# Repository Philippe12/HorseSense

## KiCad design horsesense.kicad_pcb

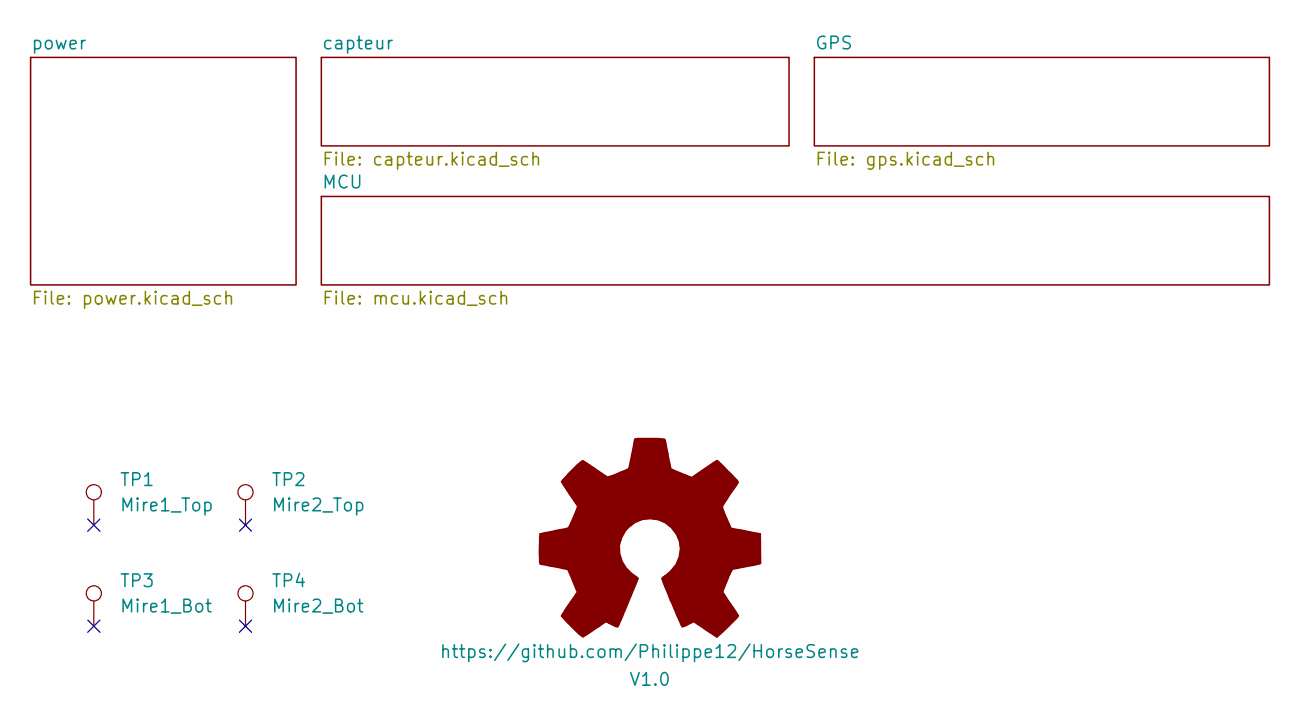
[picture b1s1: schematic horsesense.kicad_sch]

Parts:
SYM1: https://github.com/Philippe12/HorseSense; OSHW-Symbol_13.4x12mm_SilkScreen
TP1: Mire1_Top; TestPoint_Pad_D1.0mm
TP2: Mire2_Top; TestPoint_Pad_D1.0mm
TP3: Mire1_Bot; TestPoint_Pad_D1.0mm
TP4: Mire2_Bot; TestPoint_Pad_D1.0mm

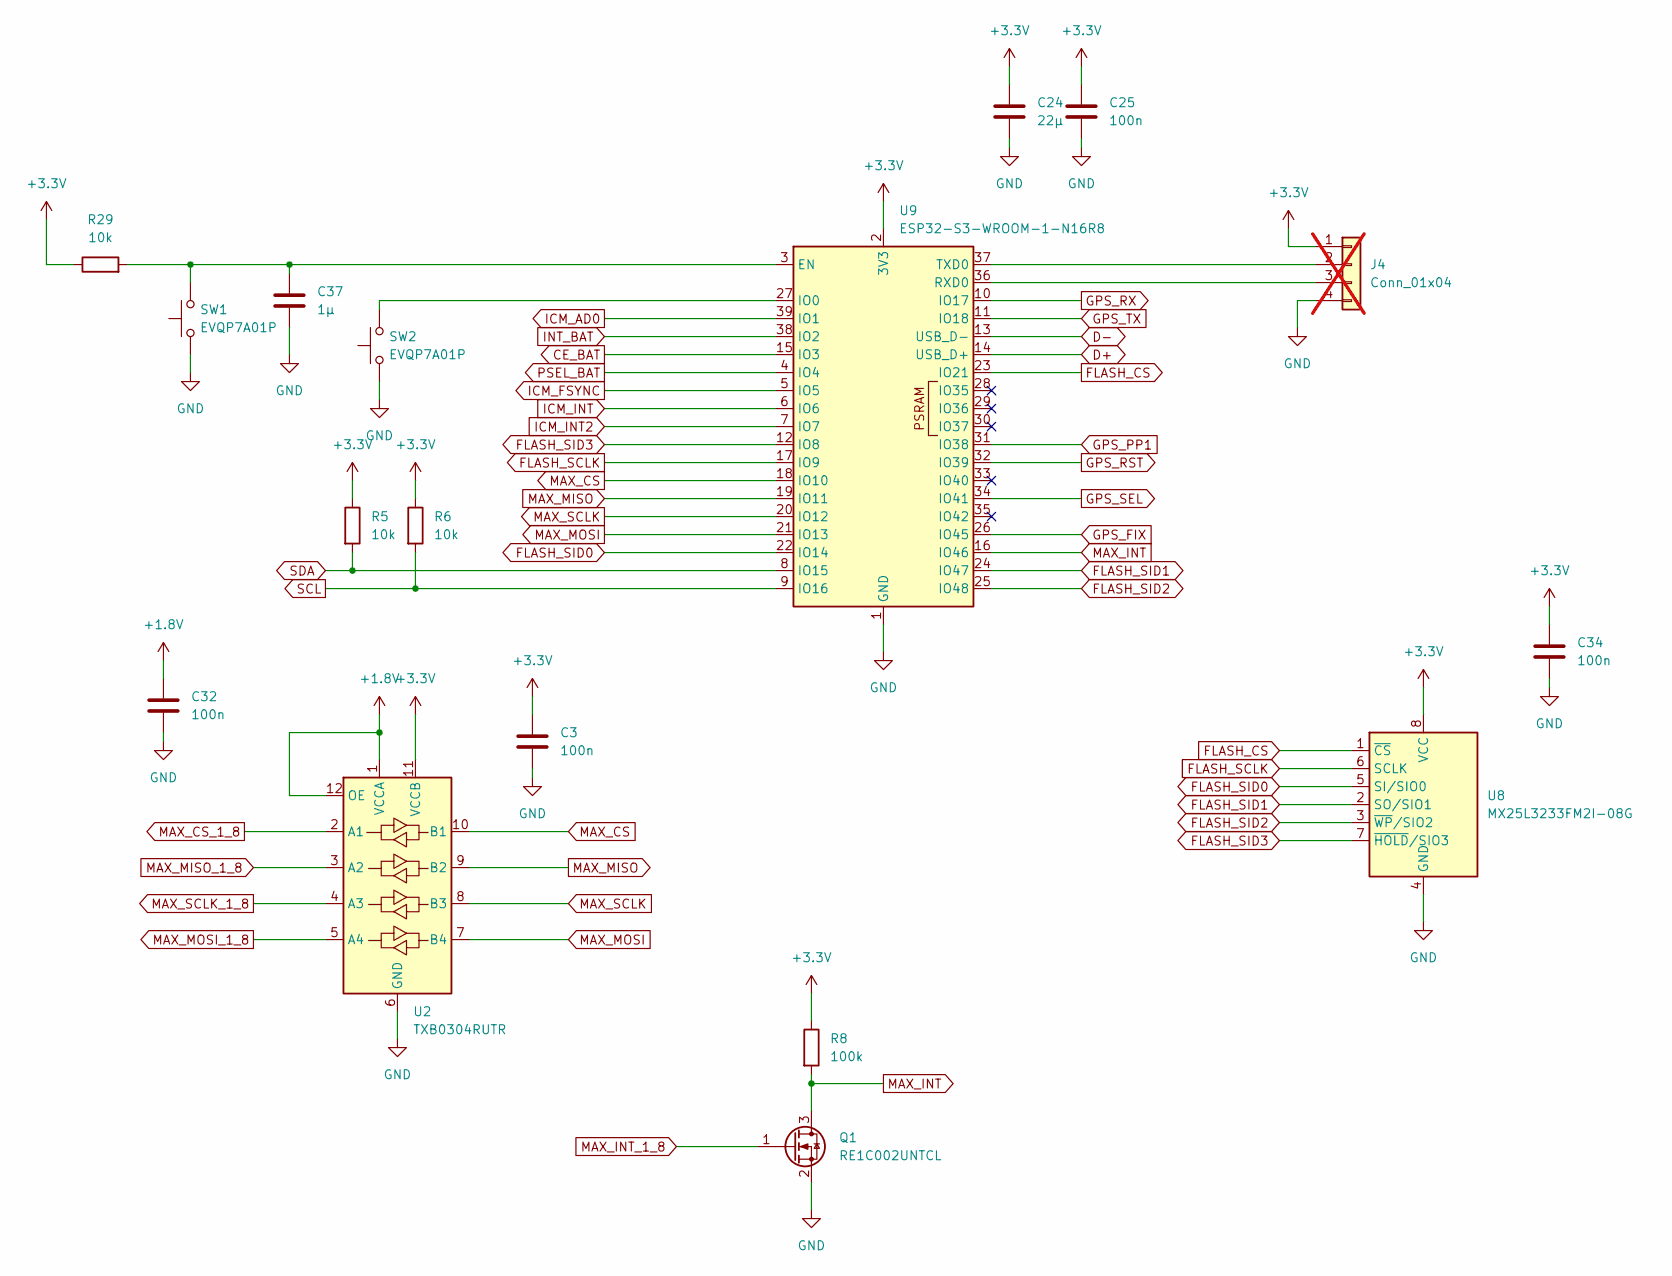
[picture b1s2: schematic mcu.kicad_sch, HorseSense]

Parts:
C3, C25, C32, C34: 100n; C_0805_2012Metric; JLCPCB Part # C1711
C24: 22µ; C_0805_2012Metric; JLCPCB Part # C907991
C37: 1µ; C_0805_2012Metric; JLCPCB Part # C1712
J4: Conn_01x04; PinHeader_1x04_P1.27mm_Vertical; not fitted
Q1: RE1C002UNTCL; SOT-416; JLCPCB Part # C509959
R5, R6, R29: 10k; R_0805_2012Metric; JLCPCB Part # C276215
R8: 100k; R_0805_2012Metric; JLCPCB Part # C25271
SW1, SW2: EVQP7A01P; SW_SPST_EVQP7A; JLCPCB Part # C79167
U2: TXB0304RUTR; Texas_R-PUQFN-N12; JLCPCB Part # C69598
U8: MX25L3233FM2I-08G; SOIC-8_5.3x5.3mm_P1.27mm; JLCPCB Part # C190802
U9: ESP32-S3-WROOM-1-N16R8; ESP32-S3-WROOM-1; JLCPCB Part # C2913202

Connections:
+1.8V: C32.1, U2.1 (VCCA), U2.12 (OE); also elsewhere on the board
+3.3V: C3.1, C24.1, C25.1, C34.1, J4.1, R5.1, R6.1, R8.1, R29.1, U2.11 (VCCB), U8.8 (VCC), U9.2 (3V3); also elsewhere on the board
CE_BAT: U9.15 (IO3); also elsewhere on the board
D+: U9.14 (USB_D+); also elsewhere on the board
D-: U9.13 (USB_D-); also elsewhere on the board
FLASH_CS: U8.1 (~CS), U9.23 (IO21)
FLASH_SCLK: U8.6 (SCLK), U9.17 (IO9)
FLASH_SID0: U8.5 (SI/SIO0), U9.22 (IO14)
FLASH_SID1: U8.2 (SO/SIO1), U9.24 (IO47)
FLASH_SID2: U8.3 (~WP/SIO2), U9.25 (IO48)
FLASH_SID3: U8.7 (~HOLD/SIO3), U9.12 (IO8)
GND: C3.2, C24.2, C25.2, C32.2, C34.2, C37.2, J4.4, Q1.2 (S), SW1.1, SW2.1, U2.6 (GND), U8.4 (GND), U9.1 (GND), U9.40 (GND), U9.41 (GND); also elsewhere on the board
GPS_FIX: U9.26 (IO45); also elsewhere on the board
GPS_PP1: U9.31 (IO38); also elsewhere on the board
GPS_RST: U9.32 (IO39); also elsewhere on the board
GPS_RX: U9.10 (IO17); also elsewhere on the board
GPS_SEL: U9.34 (IO41); also elsewhere on the board
GPS_TX: U9.11 (IO18); also elsewhere on the board
ICM_AD0: U9.39 (IO1); also elsewhere on the board
ICM_FSYNC: U9.5 (IO5); also elsewhere on the board
ICM_INT: U9.6 (IO6); also elsewhere on the board
ICM_INT2: U9.7 (IO7); also elsewhere on the board
INT_BAT: U9.38 (IO2); also elsewhere on the board
MAX_CS: U2.10 (B1), U9.18 (IO10)
MAX_CS_1_8: U2.2 (A1); also elsewhere on the board
MAX_INT: Q1.3 (D), R8.2, U9.16 (IO46)
MAX_INT_1_8: Q1.1 (G); also elsewhere on the board
MAX_MISO: U2.9 (B2), U9.19 (IO11)
MAX_MISO_1_8: U2.3 (A2); also elsewhere on the board
MAX_MOSI: U2.7 (B4), U9.21 (IO13)
MAX_MOSI_1_8: U2.5 (A4); also elsewhere on the board
MAX_SCLK: U2.8 (B3), U9.20 (IO12)
MAX_SCLK_1_8: U2.4 (A3); also elsewhere on the board
unnamed: J4.2, U9.37 (TXD0)
unnamed: J4.3, U9.36 (RXD0)
unnamed: C37.1, R29.2, SW1.2, U9.3 (EN)
unnamed: SW2.2, U9.27 (IO0)
PSEL_BAT: U9.4 (IO4); also elsewhere on the board
SCL: R6.2, U9.9 (IO16); also elsewhere on the board
SDA: R5.2, U9.8 (IO15); also elsewhere on the board

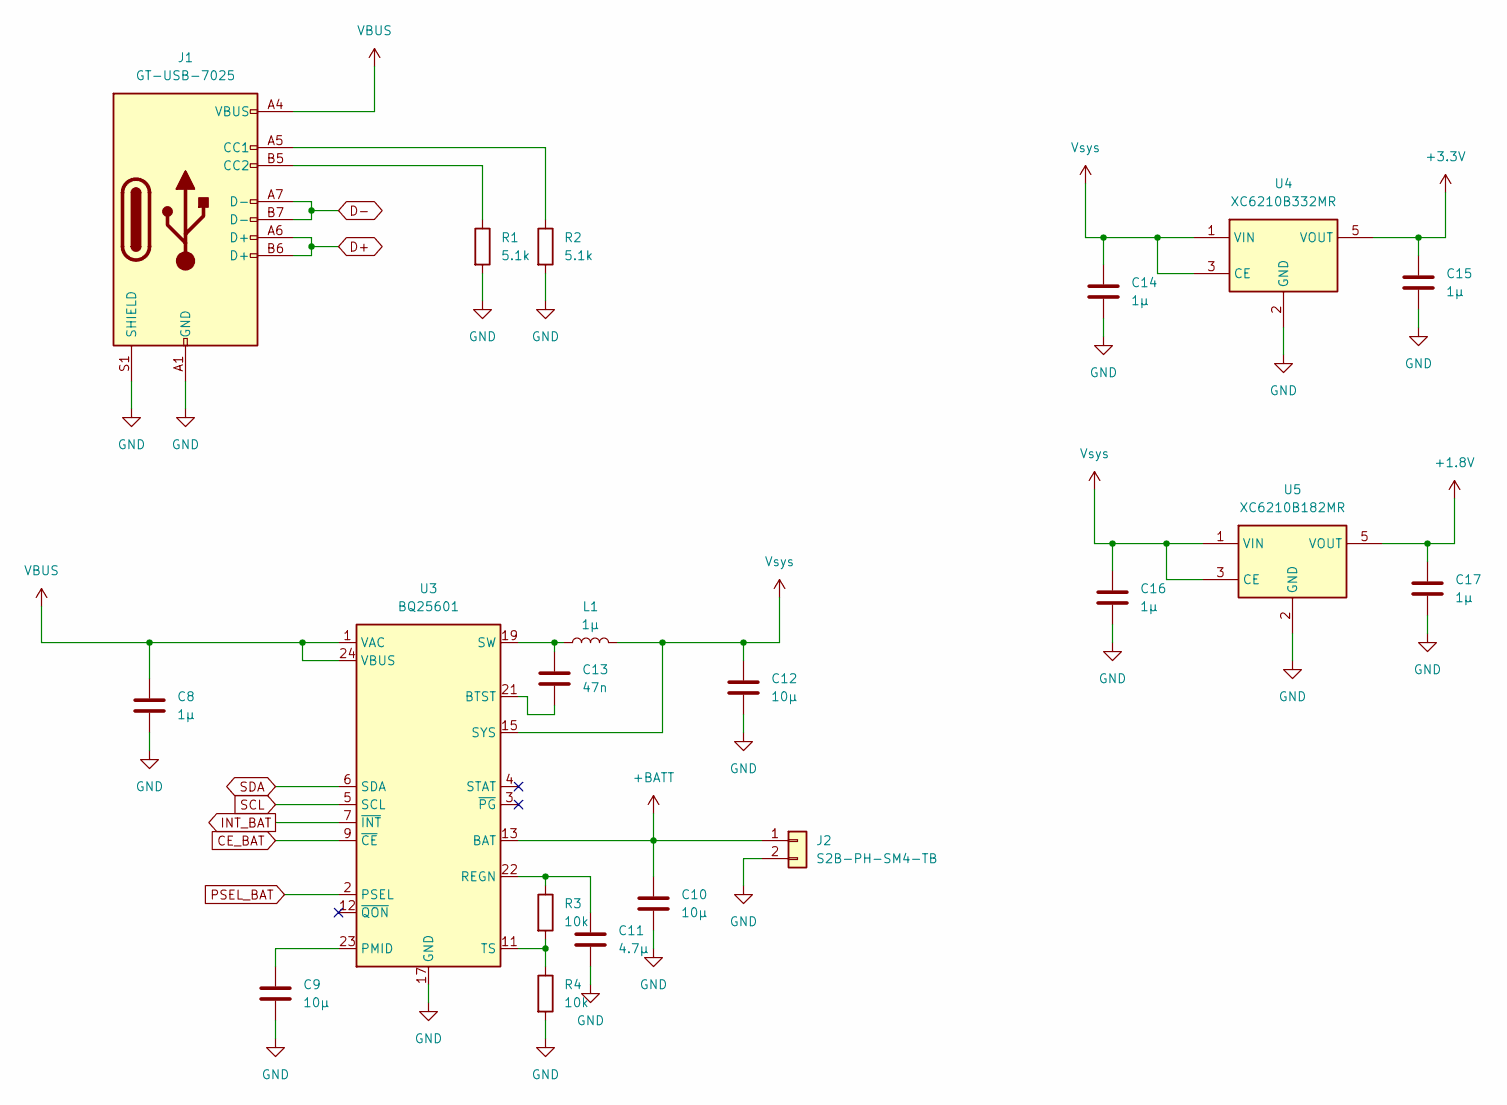
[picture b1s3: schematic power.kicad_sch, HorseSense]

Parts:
C8, C14, C15, C16, C17: 1µ; C_0805_2012Metric; JLCPCB Part # C1712
C9, C10, C12: 10µ; C_0805_2012Metric; JLCPCB Part # C32635
C11: 4.7µ; C_0805_2012Metric; JLCPCB Part # C76639
C13: 47n; C_0805_2012Metric; JLCPCB Part # C1745
J1: GT-USB-7025; USB_C_Receptacle_GCT_USB4105-xx-A_16P_TopMnt_Horizontal; JLCPCB Part # C27636760
J2: S2B-PH-SM4-TB; JST_PH_S2B-PH-SM4-TB_1x02-1MP_P2.00mm_Horizontal; JLCPCB Part # C295747
L1: 1µ; L_0805_2012Metric; JLCPCB Part # C383371
R1, R2: 5.1k; R_0805_2012Metric; JLCPCB Part # C27834
R3, R4: 10k; R_0805_2012Metric; JLCPCB Part # C276215
U3: BQ25601; Texas_RTW_WQFN-24-1EP_4x4mm_P0.5mm_EP2.7x2.7mm_ThermalVias; JLCPCB Part # C2859691
U4: XC6210B332MR; SOT-23-5; JLCPCB Part # C424705
U5: XC6210B182MR; SOT-23-5; JLCPCB Part # C2983925

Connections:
+1.8V: C17.1, U5.5 (VOUT); also elsewhere on the board
+3.3V: C15.1, U4.5 (VOUT); also elsewhere on the board
+BATT: C10.1, J2.1, U3.13 (BAT), U3.14 (BAT)
CE_BAT: U3.9 (~CE); also elsewhere on the board
D+: J1.A6 (D+), J1.B6 (D+); also elsewhere on the board
D-: J1.A7 (D-), J1.B7 (D-); also elsewhere on the board
GND: C8.2, C9.2, C10.2, C11.2, C12.2, C14.2, C15.2, C16.2, C17.2, J1.A1 (GND), J1.A12 (GND), J1.B1 (GND), J1.B12 (GND), J1.S1 (SHIELD), J2.2, R1.2, R2.2, R4.2, U3.17 (GND), U3.18 (GND), U3.25 (GND), U4.2 (GND), U5.2 (GND); also elsewhere on the board
INT_BAT: U3.7 (~INT); also elsewhere on the board
unnamed: C13.1, L1.1, U3.19 (SW), U3.20 (SW)
unnamed: J1.A5 (CC1), R2.1
unnamed: J1.B5 (CC2), R1.1
unnamed: C13.2, U3.21 (BTST)
unnamed: C9.1, U3.23 (PMID)
unnamed: C11.1, R3.1, U3.22 (REGN)
unnamed: R3.2, R4.1, U3.11 (TS)
PSEL_BAT: U3.2 (PSEL); also elsewhere on the board
SCL: U3.5 (SCL); also elsewhere on the board
SDA: U3.6 (SDA); also elsewhere on the board
VBUS: C8.1, J1.A4 (VBUS), J1.A9 (VBUS), J1.B4 (VBUS), J1.B9 (VBUS), U3.1 (VAC), U3.24 (VBUS)
Vsys: C12.1, C14.1, C16.1, L1.2, U3.15 (SYS), U3.16 (SYS), U4.1 (VIN), U4.3 (CE), U5.1 (VIN), U5.3 (CE)

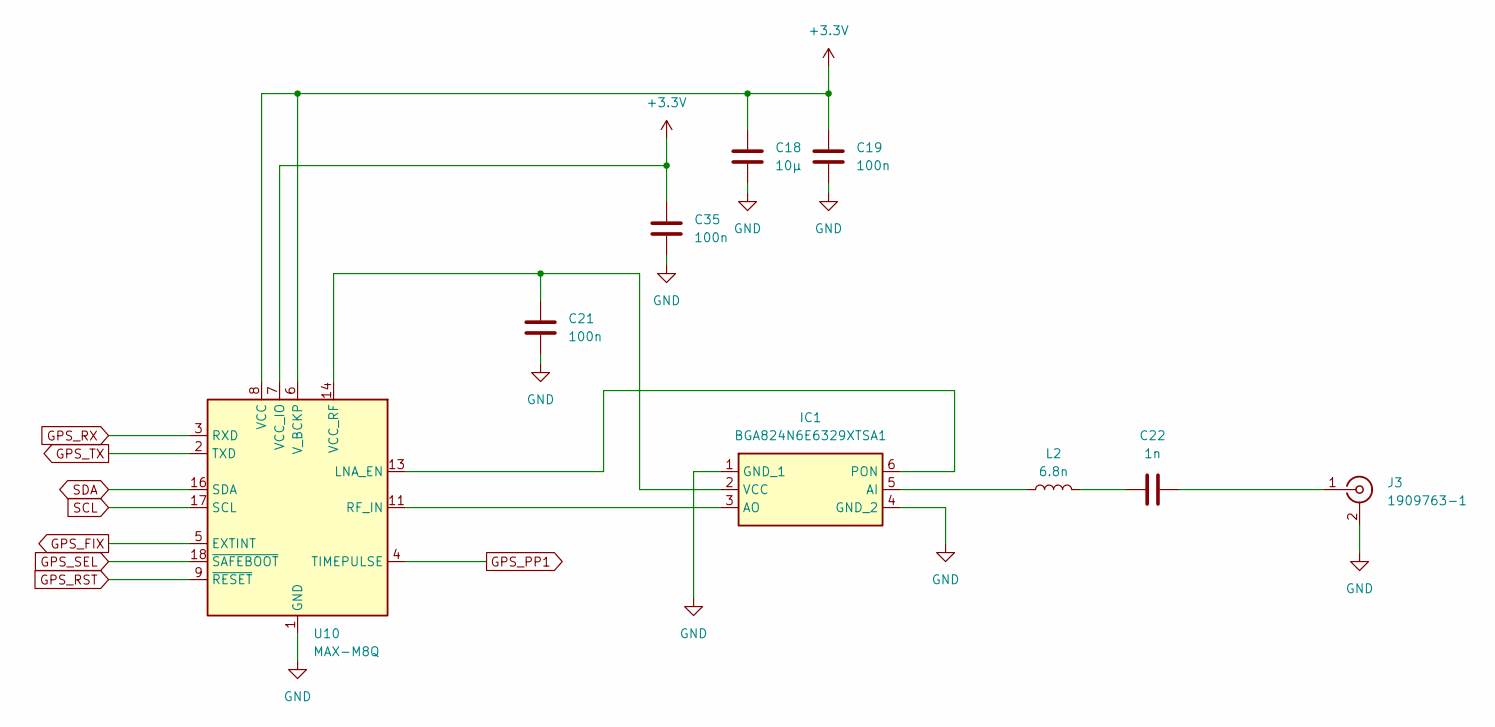
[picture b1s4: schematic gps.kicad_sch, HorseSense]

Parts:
C18: 10µ; C_0805_2012Metric; JLCPCB Part # C32635
C19, C21, C35: 100n; C_0805_2012Metric; JLCPCB Part # C1711
C22: 1n; C_0805_2012Metric; JLCPCB Part # C46653
IC1: BGA824N6E6329XTSA1; Mouser Part Number 726-BGA824N6E6329XTS
J3: 1909763-1; U.FL_Molex_MCRF_73412-0110_Vertical; JLCPCB Part # 1909763-1
L2: 6.8n; L_0805_2012Metric; JLCPCB Part # C701176
U10: MAX-M8Q; ublox_MAX; JLCPCB Part # C6898733

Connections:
+3.3V: C18.1, C19.1, C35.1, U10.6 (V_BCKP), U10.7 (VCC_IO), U10.8 (VCC); also elsewhere on the board
GND: C18.2, C19.2, C21.2, C35.2, IC1.1 (GND_1), IC1.4 (GND_2), J3.2 (Ext), U10.1 (GND), U10.10 (GND), U10.12 (GND); also elsewhere on the board
GPS_FIX: U10.5 (EXTINT); also elsewhere on the board
GPS_PP1: U10.4 (TIMEPULSE); also elsewhere on the board
GPS_RST: U10.9 (~RESET); also elsewhere on the board
GPS_RX: U10.3 (RXD); also elsewhere on the board
GPS_SEL: U10.18 (~SAFEBOOT); also elsewhere on the board
GPS_TX: U10.2 (TXD); also elsewhere on the board
unnamed: C22.1, L2.2
unnamed: IC1.5 (AI), L2.1
unnamed: IC1.3 (AO), U10.11 (RF_IN)
unnamed: IC1.6 (PON), U10.13 (LNA_EN)
unnamed: C21.1, IC1.2 (VCC), U10.14 (VCC_RF)
unnamed: C22.2, J3.1 (In)
SCL: U10.17 (SCL); also elsewhere on the board
SDA: U10.16 (SDA); also elsewhere on the board

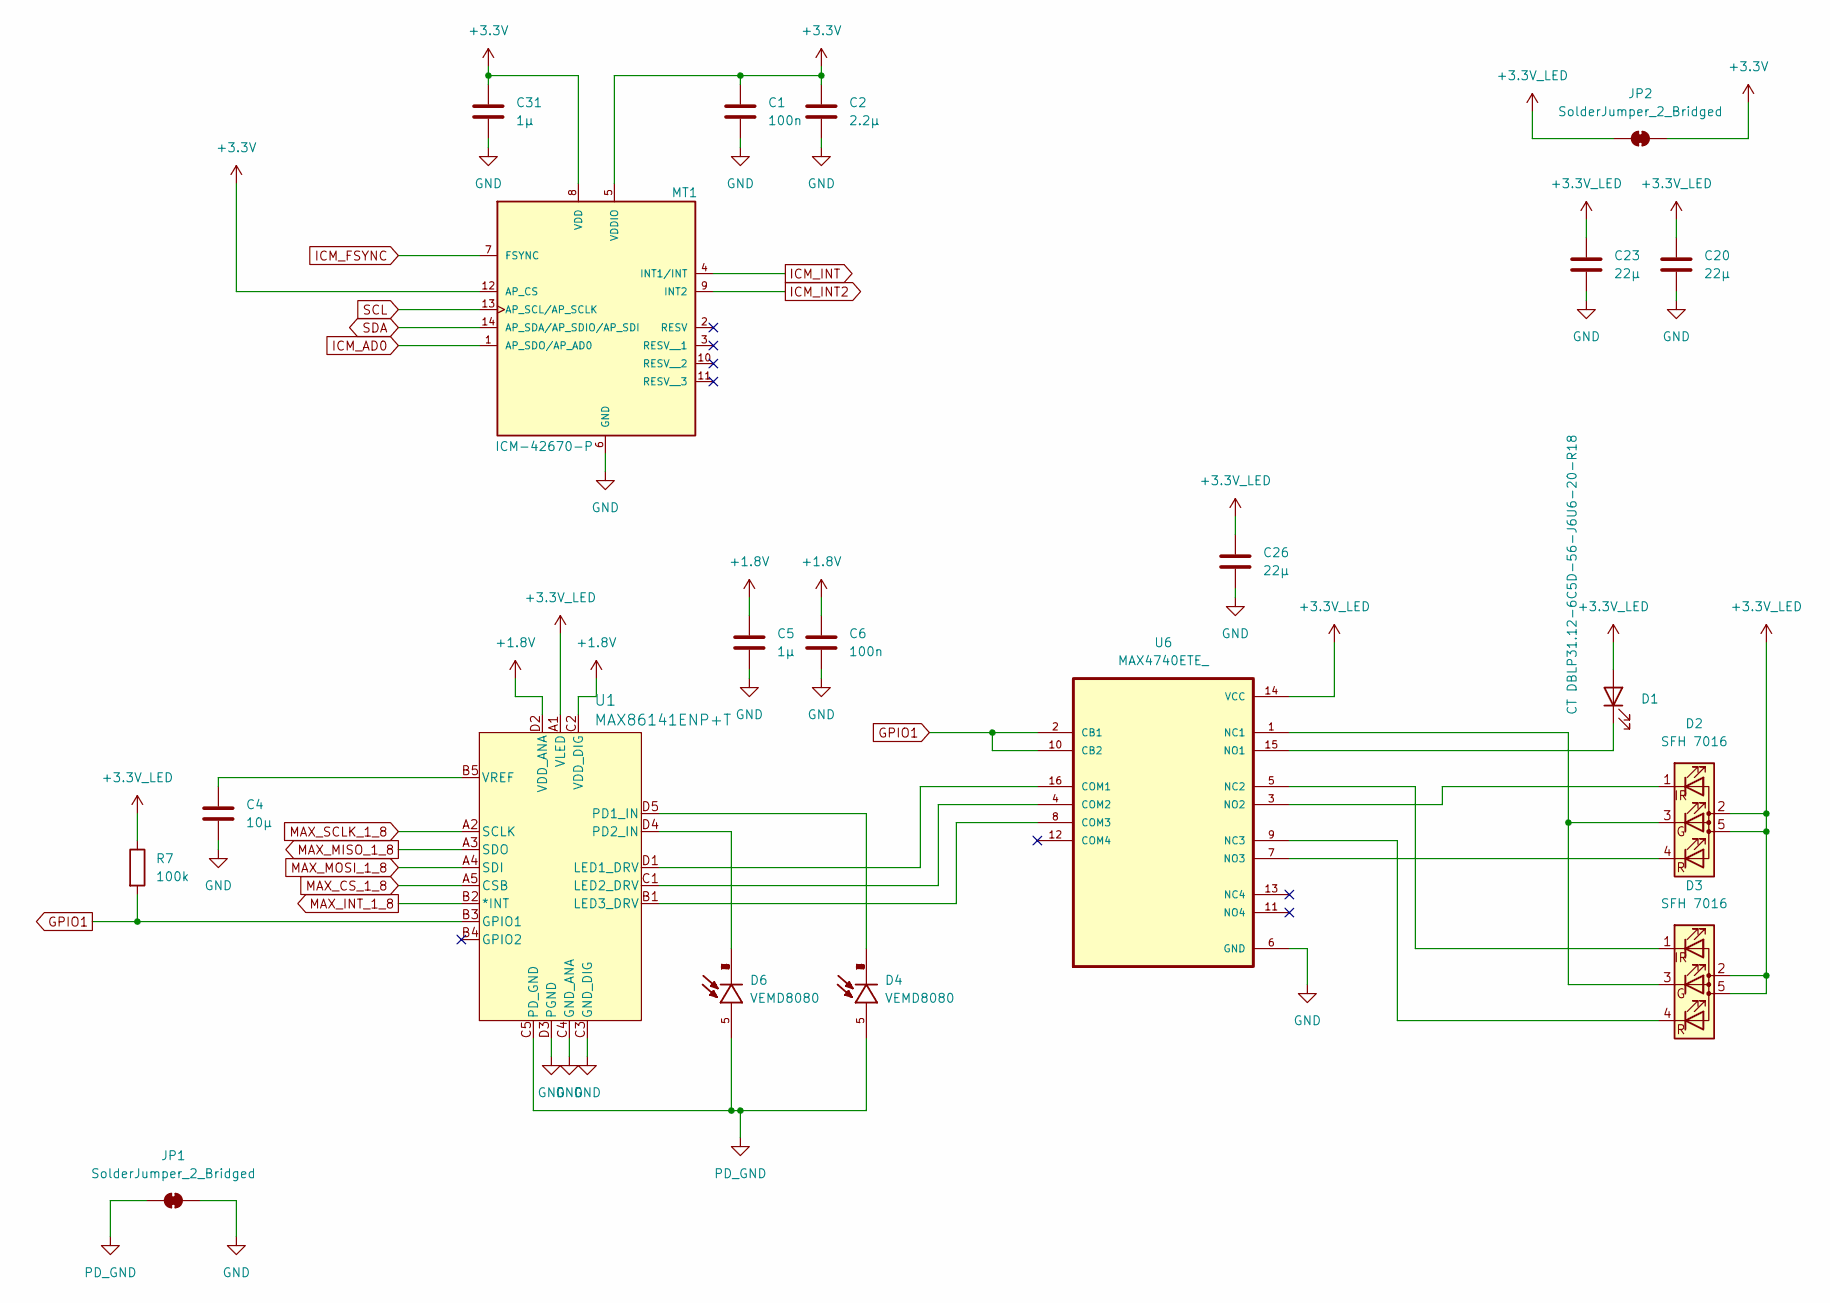
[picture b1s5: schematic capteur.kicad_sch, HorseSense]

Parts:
C1, C6: 100n; C_0805_2012Metric; JLCPCB Part # C1711
C2: 2.2µ; C_0805_2012Metric; JLCPCB Part # C19110
C4: 10µ; C_0805_2012Metric; JLCPCB Part # C32635
C5, C31: 1µ; C_0805_2012Metric; JLCPCB Part # C1712
C20, C23, C26: 22µ; C_0805_2012Metric; JLCPCB Part # C907991
D1: CT DBLP31.12-6C5D-56-J6U6-20-R18; CTDBLP31126C5D56J6U620R18; JLCPCB Part # C5603826
D2, D3: SFH 7016; SFH7016; JLCPCB Part # C2900452
D4, D6: VEMD8080; XDCR_VEMD8080; PARTREV 1.0; JLCPCB Part # C511402
JP1, JP2: SolderJumper_2_Bridged; SolderJumper-2_P1.3mm_Bridged2Bar_RoundedPad1.0x1.5mm
MT1: ICM-42670-P; XDCR_ICM-42670-P; PARTREV 1.1; JLCPCB Part # C3288646
R7: 100k; R_0805_2012Metric; JLCPCB Part # C25271
U1: MAX86141ENP+T; 21-100134_N201A2-1_MXM; JLCPCB Part # C5328762
U6: MAX4740ETE_; QFN50P300X300X80-17N; DigiKey_Part_Number MAX4740ETE+-ND

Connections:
+1.8V: C5.1, C6.1, U1.C2 (VDD_DIG), U1.D2 (VDD_ANA); also elsewhere on the board
+3.3V: C1.1, C2.1, C31.1, JP2.2 (B), MT1.5 (VDDIO), MT1.8 (VDD), MT1.12 (AP_CS); also elsewhere on the board
+3.3V_LED: C20.1, C23.1, C26.1, D1.1 (A), D2.2 (A), D2.5 (A), D3.2 (A), D3.5 (A), JP2.1 (A), R7.1, U1.A1 (VLED), U6.14 (VCC)
GND: C1.2, C2.2, C4.2, C5.2, C6.2, C20.2, C23.2, C26.2, C31.2, JP1.2 (B), MT1.6 (GND), U1.C3 (GND_DIG), U1.C4 (GND_ANA), U1.D3 (PGND), U6.6 (GND), U6.17 (GND); also elsewhere on the board
GPIO1: R7.2, U1.B3 (GPIO1), U6.2 (CB1), U6.10 (CB2)
ICM_AD0: MT1.1 (AP_SDO/AP_AD0); also elsewhere on the board
ICM_FSYNC: MT1.7 (FSYNC); also elsewhere on the board
ICM_INT: MT1.4 (INT1/INT); also elsewhere on the board
ICM_INT2: MT1.9 (INT2); also elsewhere on the board
MAX_CS_1_8: U1.A5 (CSB); also elsewhere on the board
MAX_INT_1_8: U1.B2 (*INT); also elsewhere on the board
MAX_MISO_1_8: U1.A3 (SDO); also elsewhere on the board
MAX_MOSI_1_8: U1.A4 (SDI); also elsewhere on the board
MAX_SCLK_1_8: U1.A2 (SCLK); also elsewhere on the board
unnamed: D1.2 (K), U6.15 (NO1)
unnamed: D2.4 (BK), U6.7 (NO3)
unnamed: D2.3 (GK), D3.3 (GK), U6.1 (NC1)
unnamed: D2.1 (RK), U6.3 (NO2)
unnamed: D3.4 (BK), U6.9 (NC3)
unnamed: D3.1 (RK), U6.5 (NC2)
unnamed: U1.D1 (LED1_DRV), U6.16 (COM1)
unnamed: U1.C1 (LED2_DRV), U6.4 (COM2)
unnamed: U1.B1 (LED3_DRV), U6.8 (COM3)
unnamed: D4.1, D4.2, D4.3, D4.4, D4.6, D4.7, D4.8, U1.D5 (PD1_IN)
unnamed: D6.1, D6.2, D6.3, D6.4, D6.6, D6.7, D6.8, U1.D4 (PD2_IN)
unnamed: C4.1, U1.B5 (VREF)
PD_GND: D4.5, D6.5, JP1.1 (A), U1.C5 (PD_GND)
SCL: MT1.13 (AP_SCL/AP_SCLK); also elsewhere on the board
SDA: MT1.14 (AP_SDA/AP_SDIO/AP_SDI); also elsewhere on the board

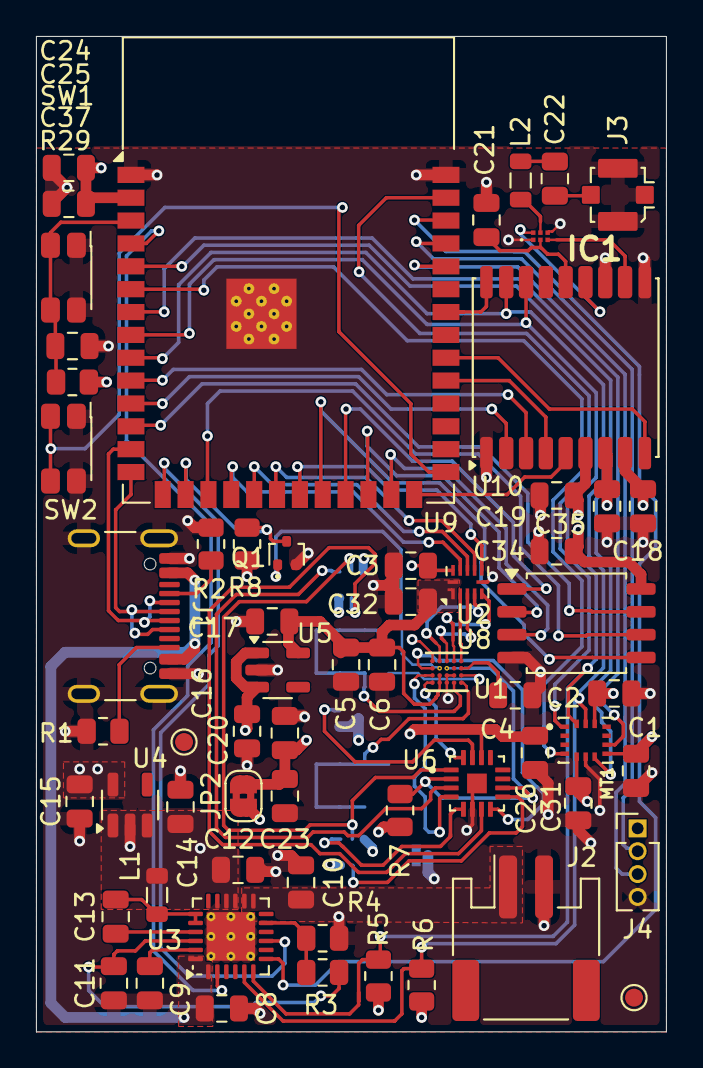
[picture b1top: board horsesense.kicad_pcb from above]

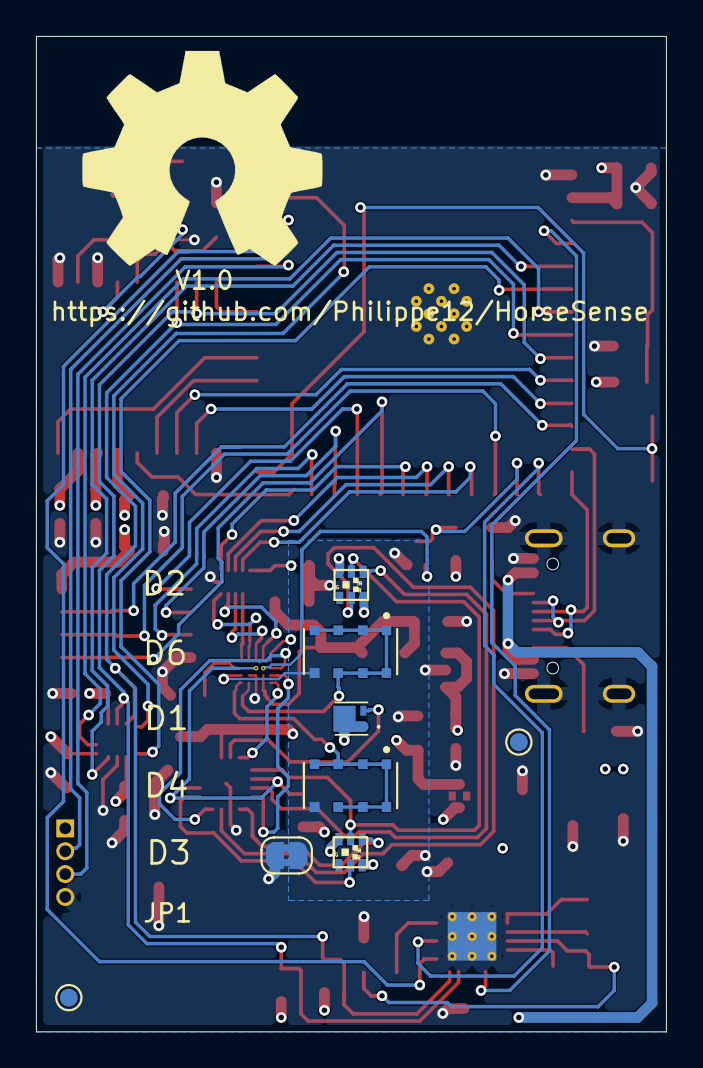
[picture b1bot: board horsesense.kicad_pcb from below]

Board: 4 copper layers, 35.0 x 55.3 mm, 71 parts (9 on the bottom side), 71 nets.

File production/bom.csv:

Designator,Footprint,Quantity,Value,LCSC Part #
"C1, C19, C21, C25, C3, C32, C34, C35, C6",0805,9,100n,C1711
"C10, C12, C18, C4, C9",0805,5,10µ,C32635
C11,0805,1,4.7µ,C76639
C13,0805,1,47n,C1745
"C14, C15, C16, C17, C31, C37, C5, C8",0805,8,1µ,C1712
C2,0805,1,2.2µ,C19110
"C20, C23, C24, C26",0805,4,22µ,C907991
C22,0805,1,1n,C46653
D1,CTDBLP31126C5D56J6U620R18,1,CT DBLP31.12-6C5D-56-J6U6-20-R18,C5603826
"D2, D3",SFH7016,2,SFH 7016,C2900452
"D4, D6",XDCR_VEMD8080,2,VEMD8080,C511402
IC1,BGA824N6E6329XTSA1,1,BGA824N6E6329XTSA1,C3191827
J1,USB_C_Receptacle_GCT_USB4105-xx-A_16P_TopMnt_Horizontal,1,GT-USB-7025,C27636760
J2,JST_PH_S2B-PH-SM4-TB_1x02-1MP_P2.00mm_Horizontal,1,S2B-PH-SM4-TB,C295747
J3,U.FL_Molex_MCRF_73412-0110_Vertical,1,1909763-1,1909763-1
L1,0805,1,1µ,C383371
L2,0805,1,6.8n,C701176
MT1,XDCR_ICM-42670-P,1,ICM-42670-P,C3288646
Q1,SOT-416,1,RE1C002UNTCL,C509959
"R1, R2",0805,2,5.1k,C27834
"R29, R3, R4, R5, R6",0805,5,10k,C276215
"R7, R8",0805,2,100k,C25271
"SW1, SW2",SW_SPST_EVQP7A,2,EVQP7A01P,C79167
U1,21-100134_N201A2-1_MXM,1,MAX86141ENP+T,C5328762
U10,ublox_MAX,1,MAX-M8Q,C6898733
U2,Texas_R-PUQFN-N12,1,TXB0304RUTR,C69598
U3,Texas_RTW_WQFN-24-1EP_4x4mm_P0.5mm_EP2.7x2.7mm_ThermalVias,1,BQ25601,C2859691
U4,SOT-23-5,1,XC6210B332MR,C424705
U5,SOT-23-5,1,XC6210B182MR,C2983925
U6,QFN50P300X300X80-17N,1,MAX4740ETE_,C1527301
U8,SOIC-8_5.3x5.3mm_P1.27mm,1,MX25L3233FM2I-08G,C190802
U9,ESP32-S3-WROOM-1,1,ESP32-S3-WROOM-1-N16R8,C2913202

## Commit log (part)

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2025-09-12 initial
2025-09-20 Create .gitignore
    ignore backup
2025-09-20 Add power rail
    Battery charger
    3.3V LDO
    1.8V LDO
2025-10-19 Routage complet
2025-10-19 Add UFL connector 3D
2025-10-19 Set MPN
2025-10-19 Change Code for JLC part
2025-10-19 JLC code chage
2025-11-01 Add Flash device
2025-11-01 Add mire and sizing marks
2025-11-01 Ass logo
2025-11-01 Add version
2025-11-01 production file
2025-11-01 3D export
2025-11-02 Change GNSS device
2025-11-23 Update for JLC parts
2025-11-23 Production files
2025-12-23 Add red and IR LED for capter
2025-12-23 Update 3D
2025-12-23 Add battery connecter
2025-12-23 export 3D board
2025-12-23 remove backup
2025-12-23 remove zip
2025-12-23 jlcpcb production part
2026-01-04 some PCB correction
2026-02-14 add data into map
2026-02-21 PCP correction CAO fitback
2026-02-21 JLC production file update
2026-02-21 Adjust C8 placement and refresh Gerbers
    Correct the placement of capacitor C8 in jlcpcb/production_files/CPL-horsesense.csv (coords changed from 15.1,1.47 to 14.375,1.255) and update jlcpcb/production_files/GERBER-horsesense.zip so the pro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
2026-02-21 Update PCB netlist and component positions
    Apply coordinate and net-mapping corrections for production PCB files: update production/netlist.ipc with numerous via coordinate adjustments and corrected net/instance entries (3.3V, GND, VBUS, VSYS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
2026-02-22 Correction from feedback jlcpcb
2026-02-22 net correction
2026-02-24 Change for µVia in pad
